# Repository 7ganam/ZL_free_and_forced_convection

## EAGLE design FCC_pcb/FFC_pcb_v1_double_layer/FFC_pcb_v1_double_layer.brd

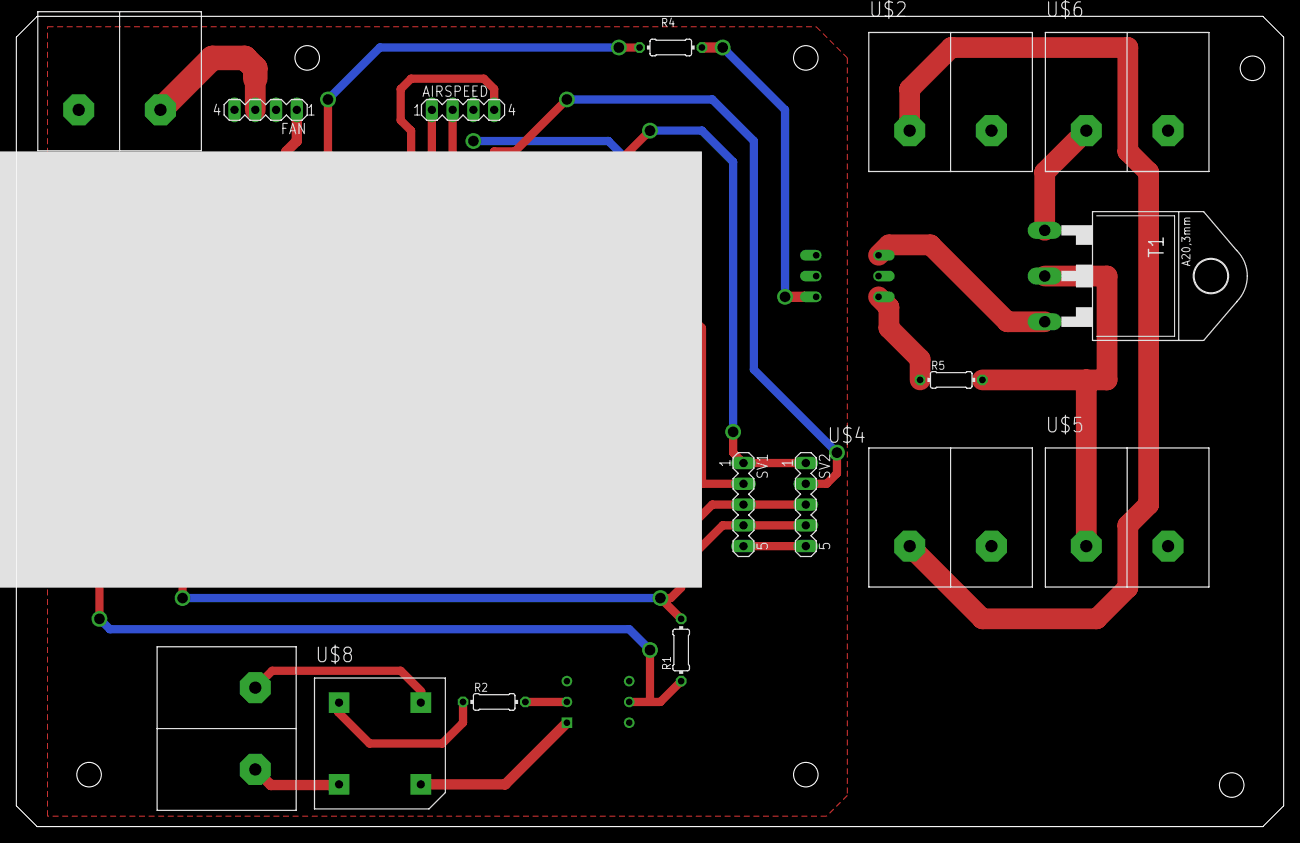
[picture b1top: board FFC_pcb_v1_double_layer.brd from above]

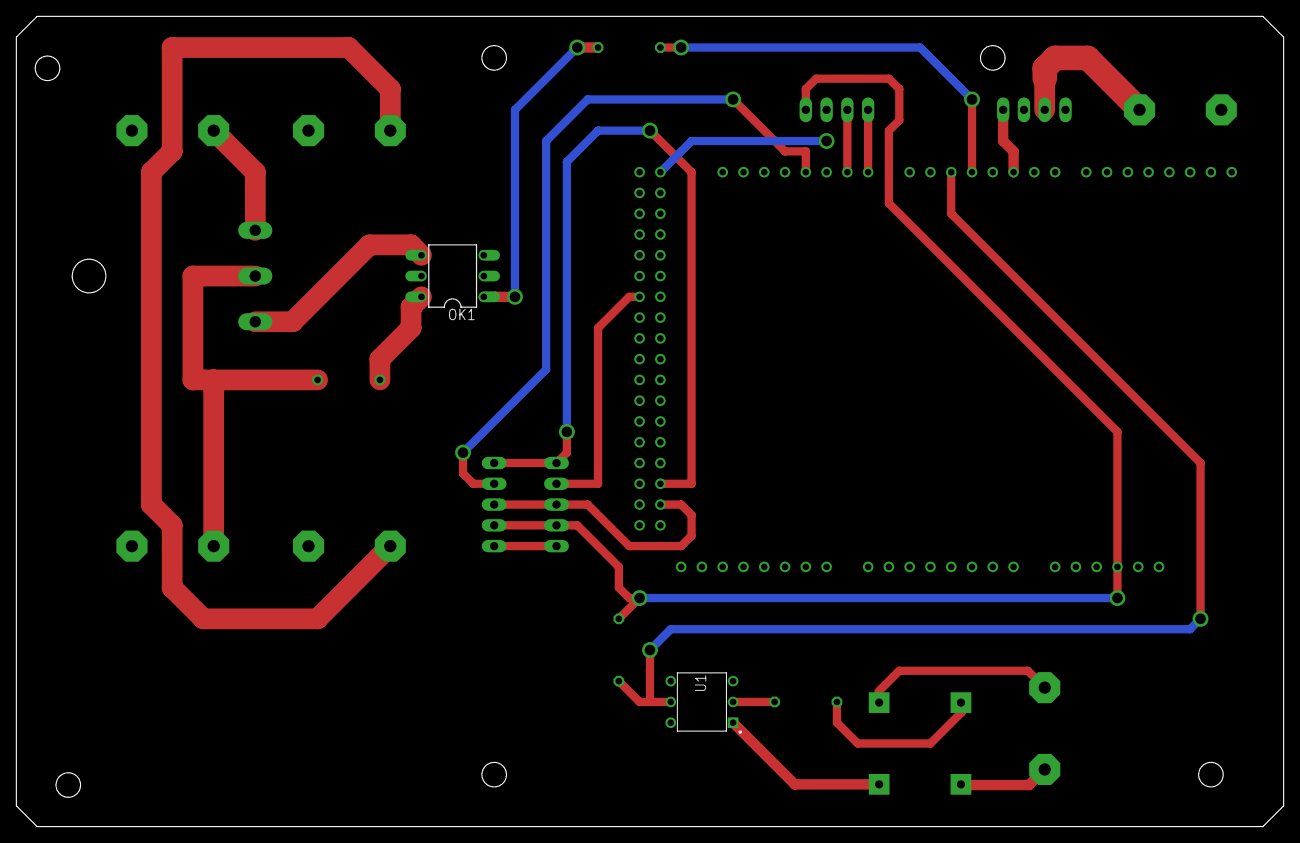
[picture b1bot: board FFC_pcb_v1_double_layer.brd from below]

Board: 2 copper layers, 154.9 x 99.1 mm, 19 parts (2 on the bottom side), 23 nets.

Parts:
AIRSPEED: MA04-1
FAN: MA04-1
OK1: MOC3022M; DIL06
R1, R2, R4, R5: 0204/7
SV1: thermo1; MA05-1
SV2: thermo2; MA05-1
T1: BTA26-H; TOP3L-1
U1: 4N25; DIP762W50P254L712H400Q6N
U$1: MEGA_DEVICE; MEGABOX
U$2: heater_ground; COVERED_TERMINAL_2PINS
U$3: 12vac; COVERED_TERMINAL_2PINS
U$4: ground220; COVERED_TERMINAL_2PINS
U$5: hot220; COVERED_TERMINAL_2PINS
U$6: heater_hot; COVERED_TERMINAL_2PINS
U$7: 12VDC; COVERED_TERMINAL_2PINS
U$8: BRIDGE

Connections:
GND: AIRSPEED.3, FAN.4, OK1.2, SV1.5, SV2.5, U1.4, U$1.GND@4, U$7.1
unnamed: R1.1, U1.5, U$1.2
unnamed: OK1.6, R5.1
unnamed: U1.1, U$8.2
unnamed: R4.1, U$1.3
unnamed: OK1.1, R4.2
unnamed: R5.2, T1.A2, U$5.1
unnamed: T1.A1, U$6.1
unnamed: R2.1, U$8.4
unnamed: OK1.4, T1.G
unnamed: U$2.1, U$4.1
unnamed: U$3.1, U$8.1
unnamed: U$3.2, U$8.3
unnamed: R2.2, U1.2
unnamed: SV2.2, U$1.17
unnamed: FAN.1, U$1.5
unnamed: FAN.3, U$7.2
unnamed: SV1.2, U$1.33
unnamed: AIRSPEED.4, R1.2, SV1.4, SV2.4, U$1.5V
unnamed: SV1.3, SV2.3, U$1.52
unnamed: AIRSPEED.2, U$1.15
unnamed: AIRSPEED.1, U$1.14
unnamed: SV1.1, SV2.1, U$1.50

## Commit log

2020-04-23 added all old file to the repo
